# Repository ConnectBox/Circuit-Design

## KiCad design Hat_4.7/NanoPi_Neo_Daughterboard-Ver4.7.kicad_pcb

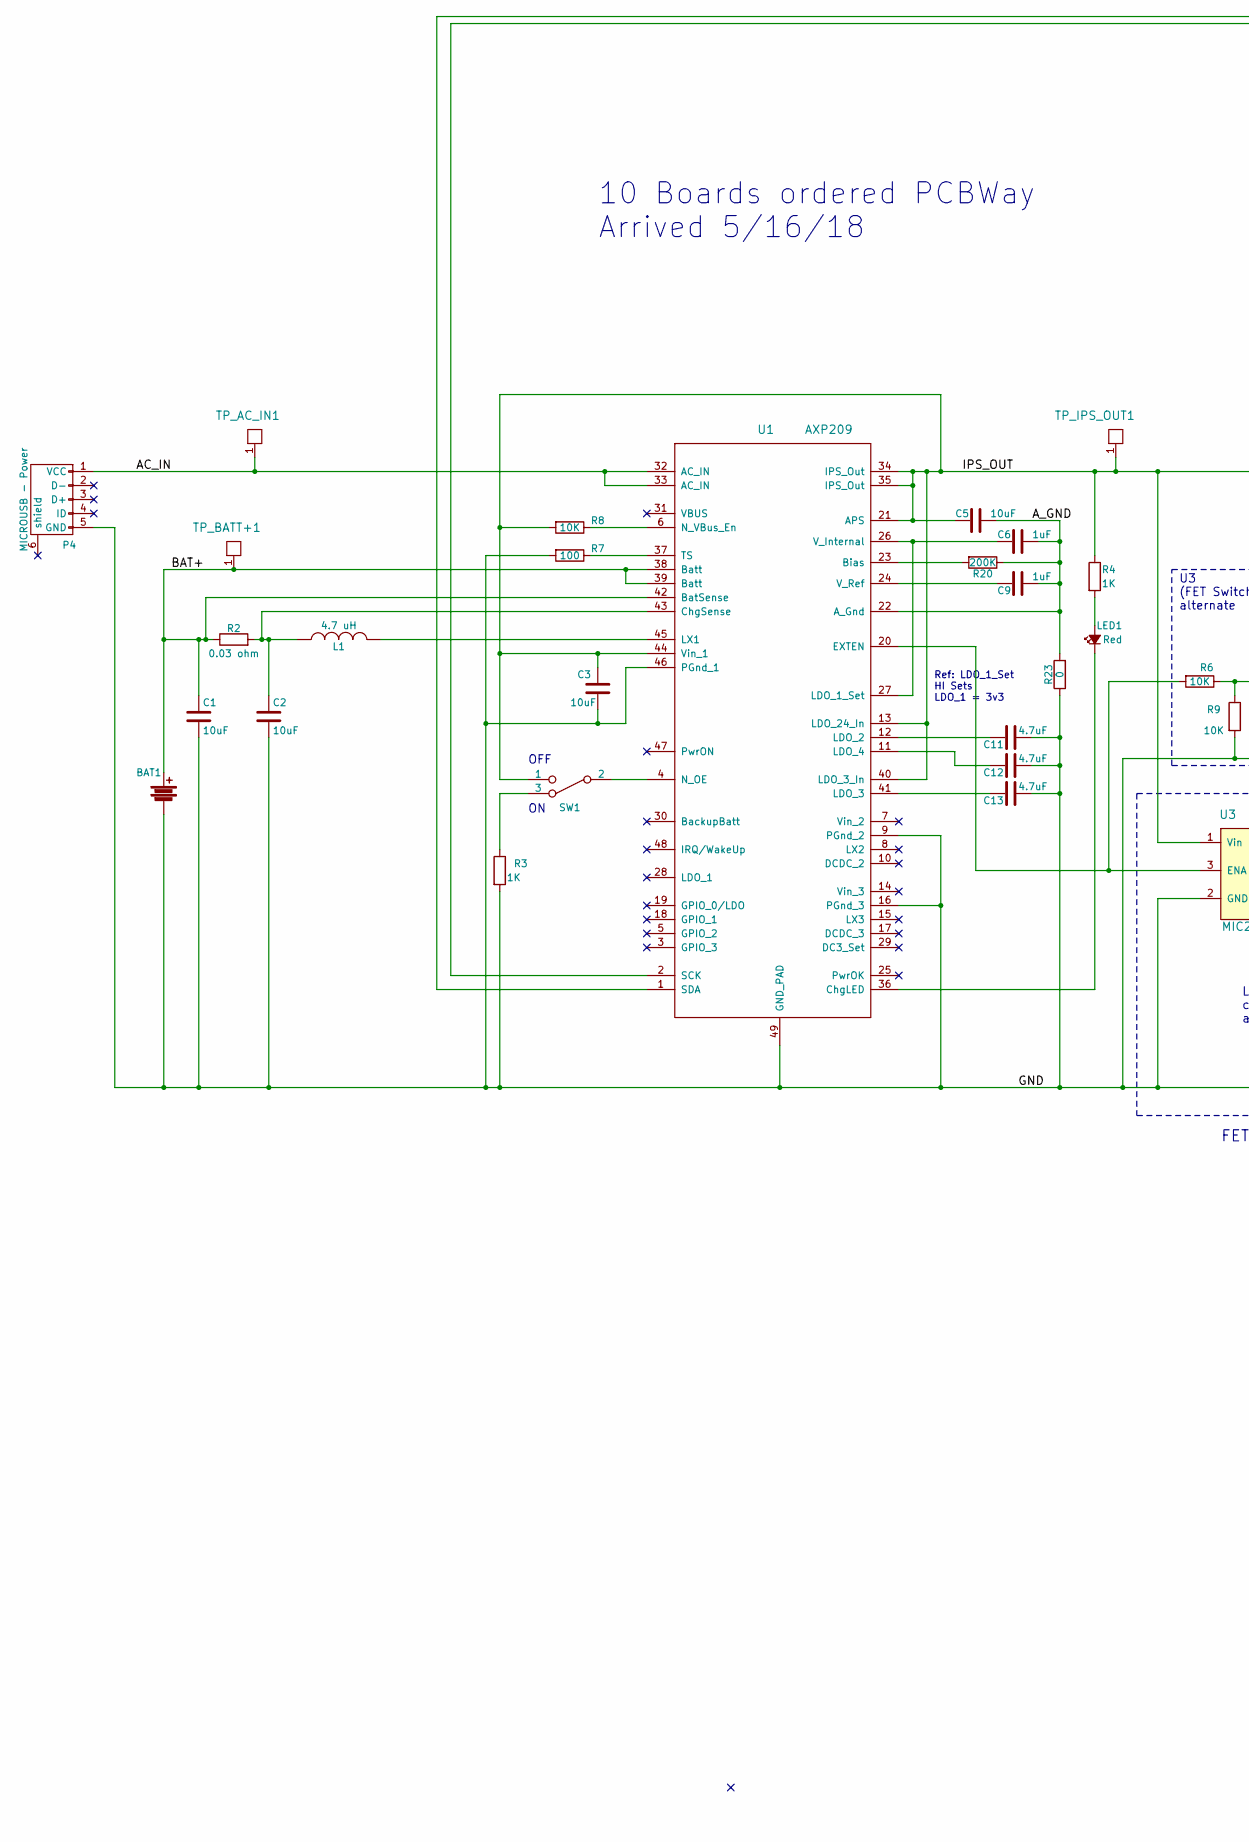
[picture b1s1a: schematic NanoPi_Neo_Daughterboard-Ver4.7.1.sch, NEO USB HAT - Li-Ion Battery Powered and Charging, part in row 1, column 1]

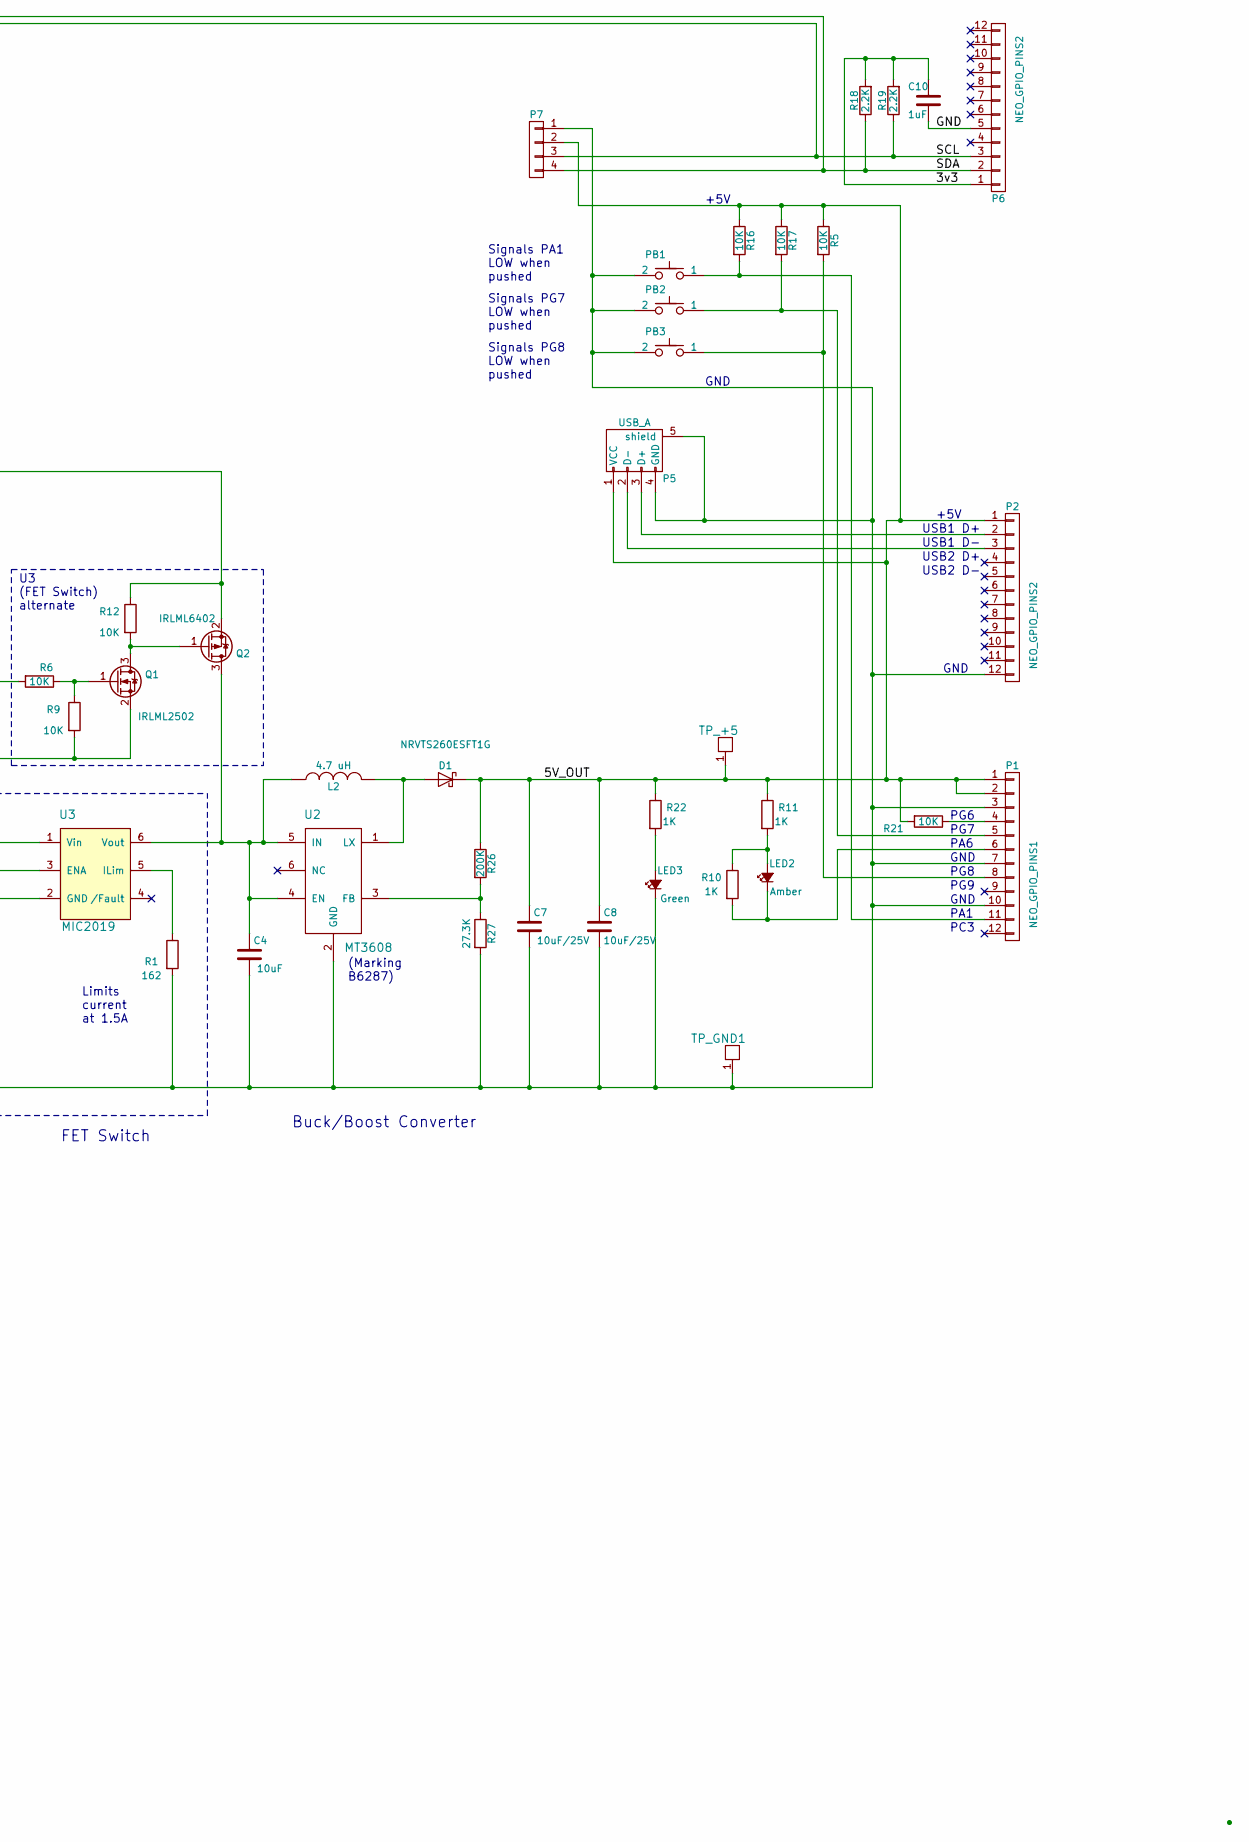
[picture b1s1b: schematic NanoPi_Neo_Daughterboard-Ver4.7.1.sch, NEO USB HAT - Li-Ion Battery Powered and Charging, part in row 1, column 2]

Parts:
BAT1: Battery; Molex_53261
C1, C2, C3, C4, C5: 10uF; C_0805
C6, C9, C10: 1uF; C_0805
C7, C8: 10uF/25V; C_0805
C11, C12, C13: 4.7uF; C_0805
D1: NRVTS260ESFT1G; SMA_Standard
L1, L2: 4.7 uH; INDUCTOR_SMD_6x6-1
LED1: Red; LED_0603
LED2: Amber; LED_0603
LED3: Green; LED_0603
P1: NEO_GPIO_PINS1; PinStrip_12-N
P2: NEO_GPIO_PINS2; PinStrip_12
P4: MICROUSB - Power; USB_Micro-B_Molex_47346-0001
P5: USB_A
P6: NEO_GPIO_PINS2; PinStrip_12-N
P7: CONN_01X04; OLED
PB1, PB2, PB3: SPST-PUSH; SW-TL3305
Q1: IRLML2502; SOT-23
Q2: IRLML6402; SOT-23
R1: 162; R_0805
R2: 0.03 ohm; R_0805
R3, R4, R10, R11, R22: 1K; R_0805
R5, R6, R8, R9, R12, R16, R17, R21: 10K; R_0805
R7: 100; R_0805
R18, R19: 2.2K; R_0805
R20, R26: 200K; R_0805
R23: 0; R_0805
R27: 27.3K; R_0805
SW1: SPDT-2C; SPDT-OS10211
TP_+5: TestPoint; ProbePad
TP_AC_IN1: TestPoint; ProbePad
TP_BATT+1: TestPoint; ProbePad
TP_GND1: TestPoint; ProbePad
TP_IPS_OUT1: TestPoint; ProbePad
U1: AXP209; UQFN-48-1EP_6x6mm_Pitch0.4mm
U2: MT3608; SOT-23-6a
U3: MIC2019; SOT-23-6a

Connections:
/3v3: C10.1, P6.1, R18.2, R19.2
/5V_OUT: C7.1, C8.1, D1.1 (K), P1.1, P1.2, P2.1, P5.1 (VCC), P7.2, R5.1, R11.1, R16.1, R17.1, R21.2, R22.1, R26.1, TP_+5.1; also elsewhere on the board
/AC_IN: P4.1 (VCC), TP_AC_IN1.1, U1.32 (AC_IN), U1.33 (AC_IN)
/A_GND: C5.1, C6.1, C9.1, R20.1, R23.2, U1.22 (A_Gnd)
/BAT+: BAT1.1, C1.1, R2.1, TP_BATT+1.1, U1.38 (Batt), U1.39 (Batt), U1.42 (BatSense)
/GND: BAT1.2, C1.2, C2.2, C3.2, C4.2, C7.2, C8.2, C10.2, C11.1, C12.1, C13.1, LED3.1 (K), P1.3, P1.7, P1.10, P2.12, P4.5 (GND), P5.4 (GND), P5.5 (shield), P6.5, P7.1, PB1.2, PB2.2, PB3.2, Q1.2 (S), R1.2, R3.2, R7.2, R9.2, R23.1, R27.2, TP_GND1.1, U1.9 (PGnd_2), U1.16 (PGnd_3), U1.46 (PGnd_1), U1.49 (GND_PAD), U2.2 (GND), U3.2 (GND); also elsewhere on the board
/IPS_OUT: C3.1, C5.2, Q2.2 (S), R4.1, R8.2, R12.1, SW1.1, TP_IPS_OUT1.1, U1.13 (LDO_24_In), U1.21 (APS), U1.34 (IPS_Out), U1.35 (IPS_Out), U1.40 (LDO_3_In), U1.44 (Vin_1), U3.1 (Vin)
/SCL: P6.3, P7.3, R19.1, U1.2 (SCK)
/SDA: P6.2, P7.4, R18.1, U1.1 (SDA)
unnamed: C2.1, L1.1, R2.2, U1.43 (ChgSense)
unnamed: C4.1, L2.1, Q2.3 (D), U2.4 (EN), U2.5 (IN), U3.6 (Vout)
unnamed: C6.2, U1.26 (V_Internal), U1.27 (LDO_1_Set)
unnamed: C9.2, U1.24 (V_Ref)
unnamed: C11.2, U1.12 (LDO_2)
unnamed: C12.2, U1.11 (LDO_4)
unnamed: C13.2, U1.41 (LDO_3)
unnamed: D1.2 (A), L2.2, U2.1 (LX)
unnamed: L1.2, U1.45 (LX1)
unnamed: LED1.1 (K), U1.36 (ChgLED)
unnamed: LED1.2 (A), R4.2
unnamed: LED2.1 (K), P1.6, R10.2
unnamed: LED2.2 (A), R10.1, R11.2
unnamed: LED3.2 (A), R22.2
unnamed: P1.4, R21.1
unnamed: P1.5, PB2.1, R17.2
unnamed: P1.8, PB3.1, R5.2
unnamed: P1.11, PB1.1, R16.2
unnamed: P2.2, P5.3 (D+)
unnamed: P2.3, P5.2 (D-)
unnamed: Q1.1 (G), R6.1, R9.1
unnamed: Q1.3 (D), Q2.1 (G), R12.2
unnamed: R1.1, U3.5 (ILim)
unnamed: R3.1, SW1.3
unnamed: R6.2, U1.20 (EXTEN), U3.3 (ENA)
unnamed: R7.1, U1.37 (TS)
unnamed: R8.1, U1.6 (N_VBus_En)
unnamed: R20.2, U1.23 (Bias)
unnamed: R26.2, R27.1, U2.3 (FB)
unnamed: SW1.2, U1.4 (N_OE)

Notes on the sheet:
GND
+5V
USB1 D+
USB1 D-
USB2 D+
USB2 D-
PA6
Buck/Boost Converter
PG6
PG7
PG8
PG9
GND
PA1
PC3
Signals PA1 LOW when pushed
Signals PG7 LOW when pushed
OFF
Ref: LDO_1_Set HI Sets LDO_1 = 3v3
Limits current at 1.5A
(Marking B6287)
Signals PG8 LOW when pushed
U3 (FET Switch) alternate
FET Switch
10 Boards ordered PCBWay Arrived 5/16/18

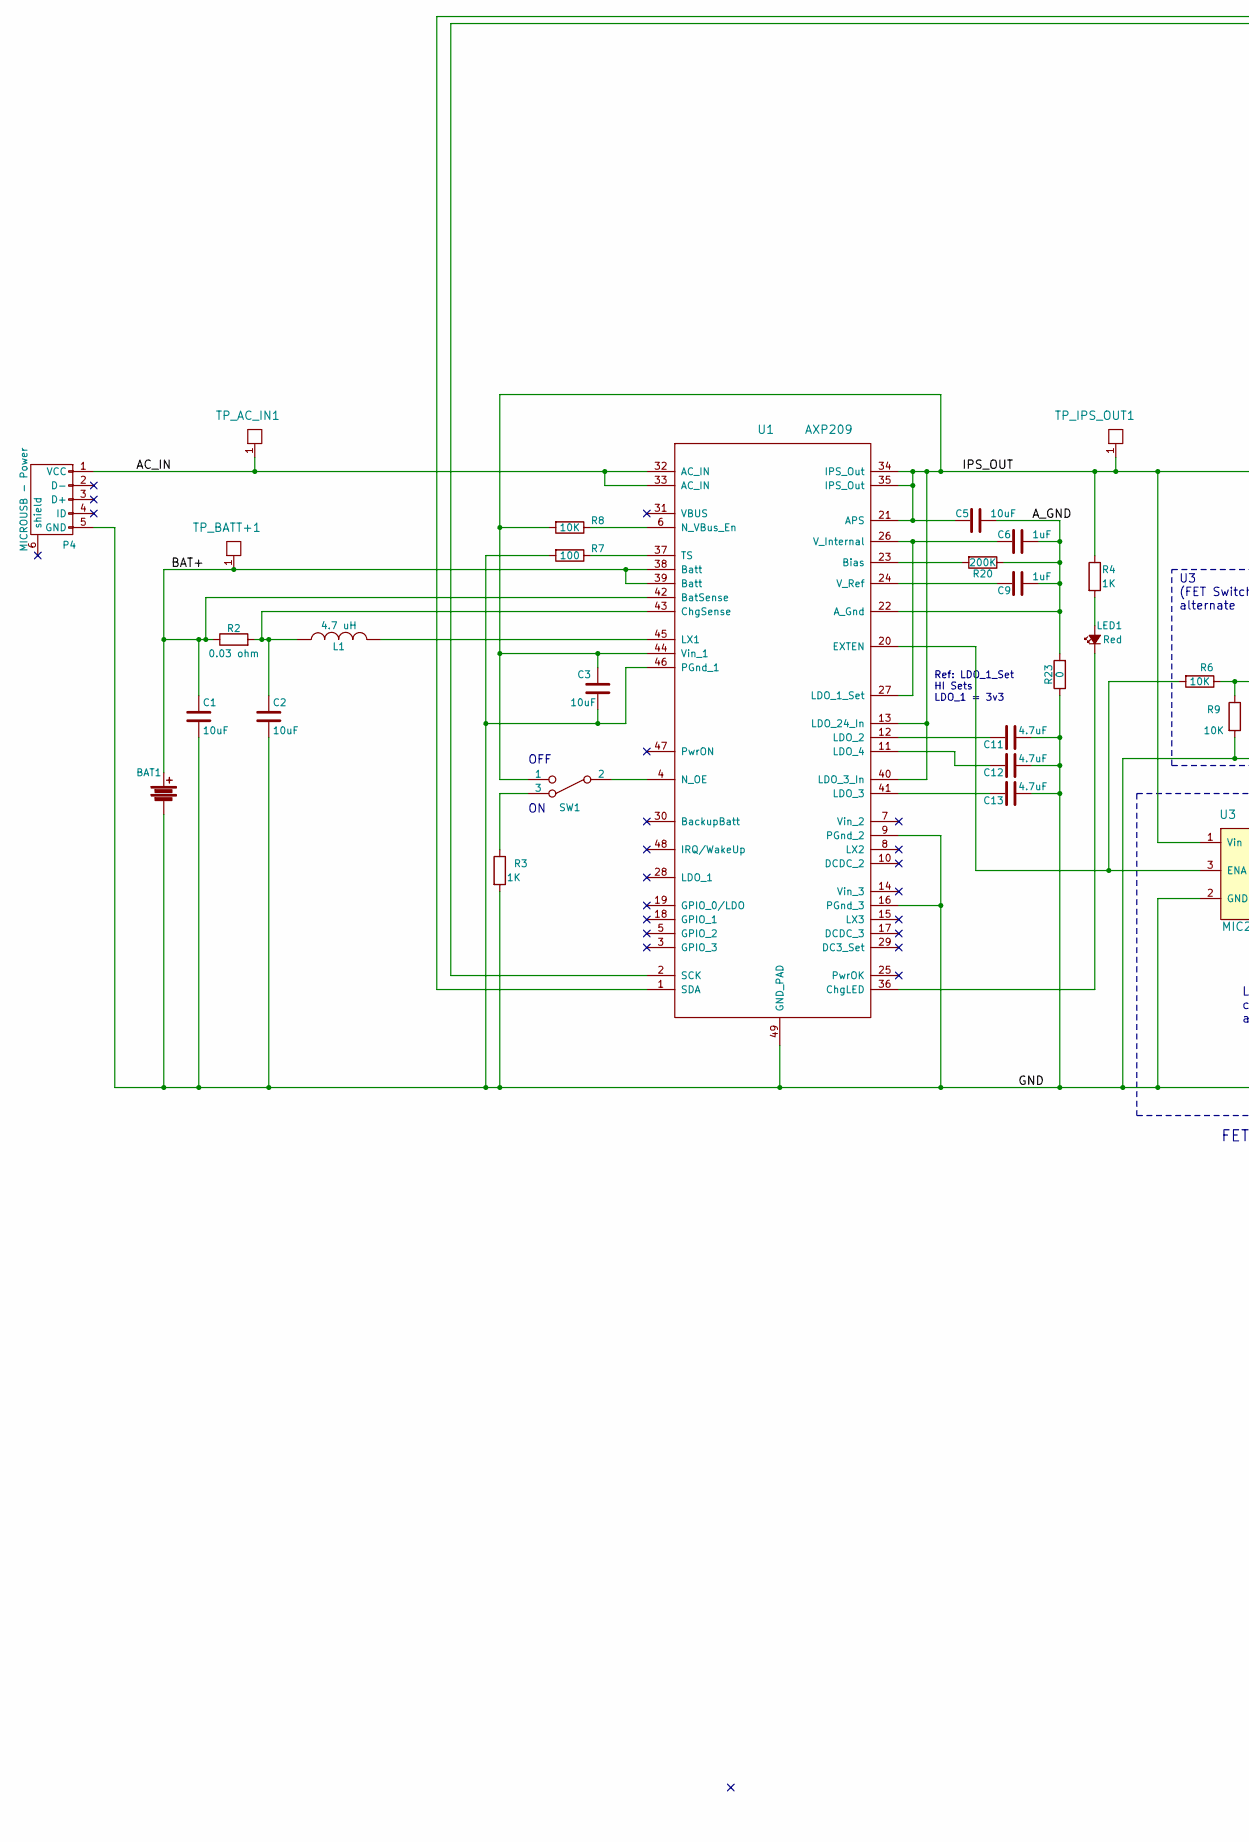
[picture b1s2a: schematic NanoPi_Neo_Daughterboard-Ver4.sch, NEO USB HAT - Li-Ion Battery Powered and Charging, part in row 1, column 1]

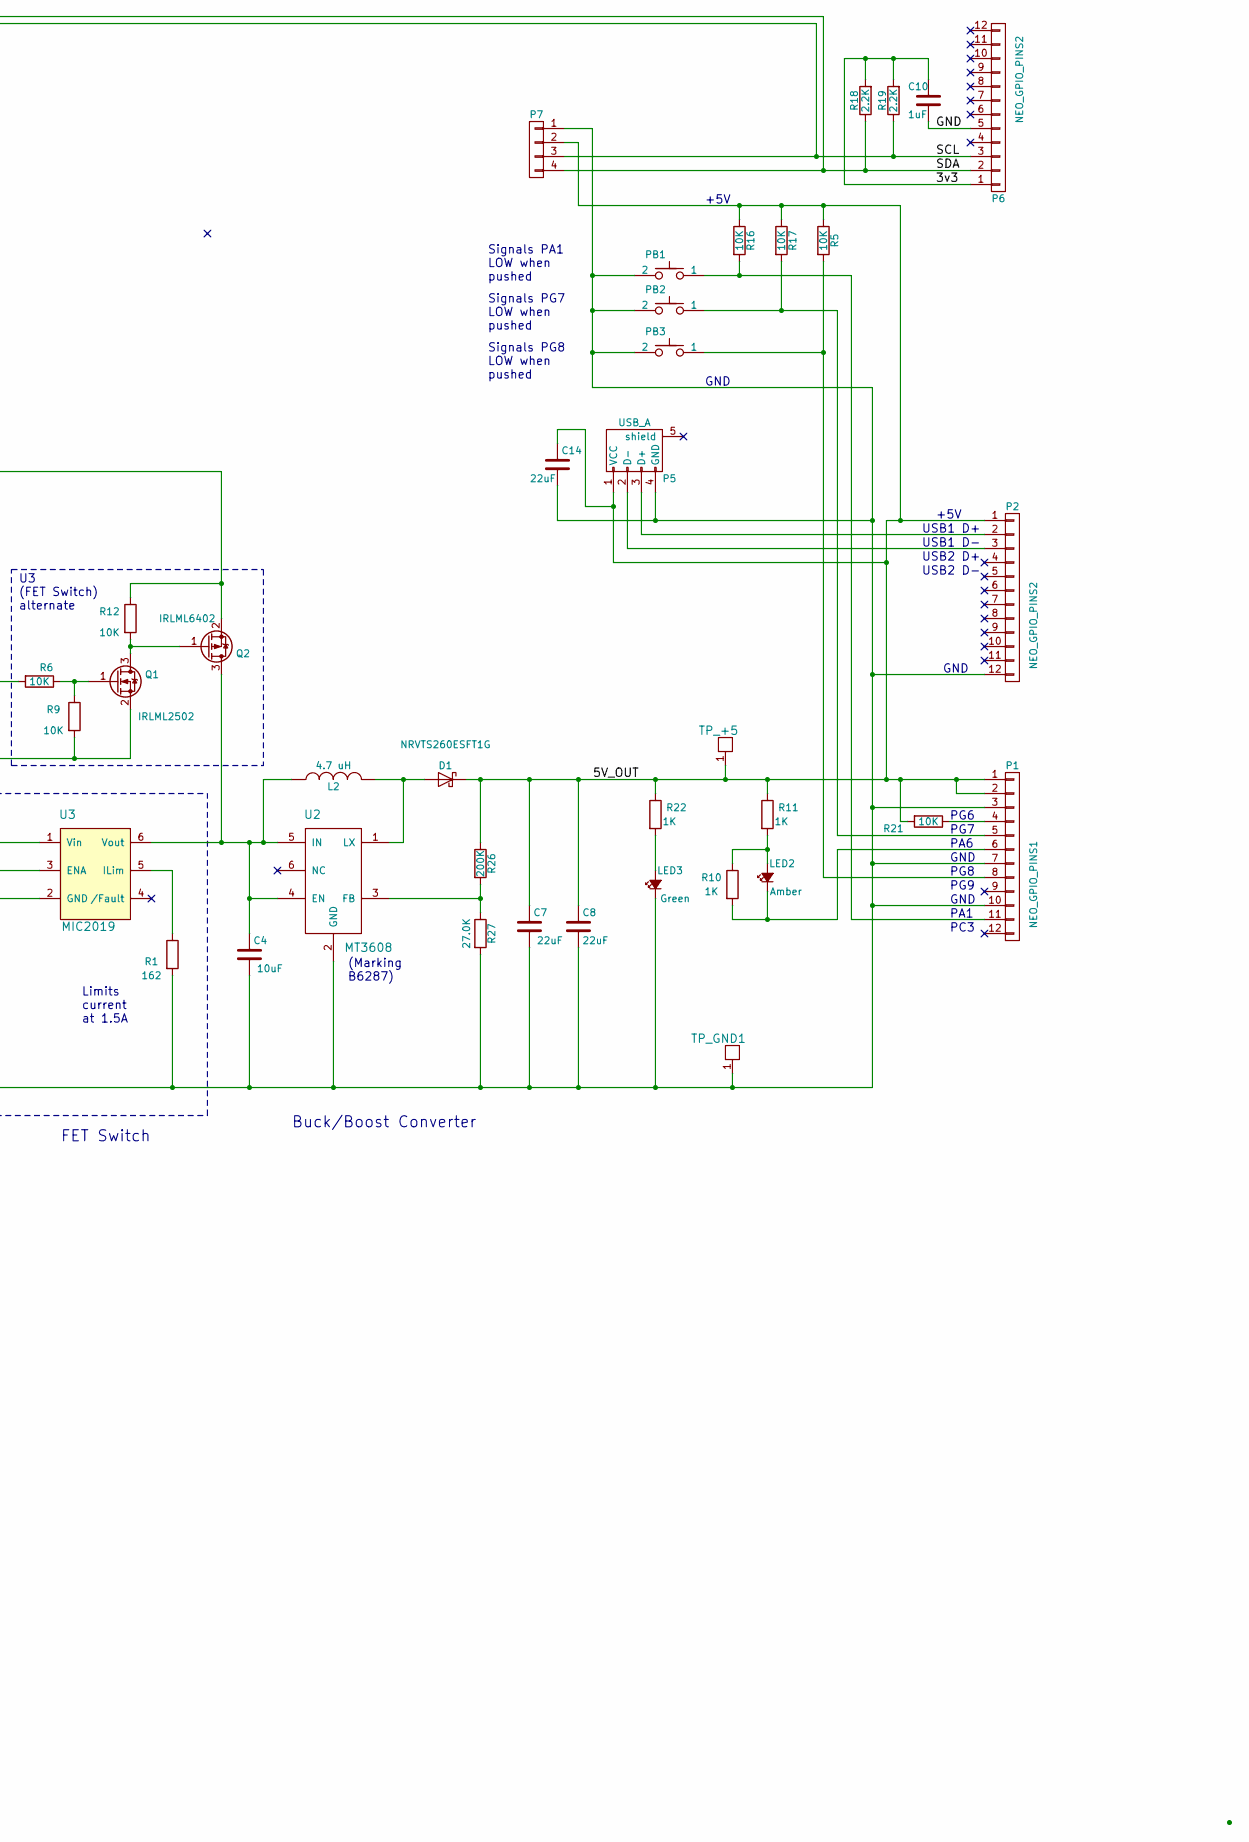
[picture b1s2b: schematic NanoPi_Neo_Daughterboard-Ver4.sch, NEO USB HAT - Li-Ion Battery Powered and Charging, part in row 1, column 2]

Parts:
BAT1: Battery; Molex_53261; Manufacturer P/N 0532610271; DigiKey P/N WM7620CT-ND
C1, C2, C3, C4, C5: 10uF; C_0805; Manufacturer P/N CL21A106MPFNNNE; DigiKey P/N 1276-1144-1-ND
C6, C9, C10: 1uF; C_0805; Manufacturer P/N C0805C105K8PACTU; DigiKey P/N 399-8006-1-ND
C7, C8, C14: 22uF; C_0805; Manufacturer P/N C0805C226M8PAC7800; DigiKey P/N 399-12069-1-ND
C11, C12, C13: 4.7uF; C_0805; Manufacturer P/N CL21B475KPFNNNE; DigiKey P/N 1276-2972-1-ND
D1: NRVTS260ESFT1G; SOD-123FL; Manufacturer P/N NRVTS260ESFT1G; DigiKey P/N NRVTS260ESFT1GOSCT-ND
L1, L2: 4.7 uH; INDUCTOR_SMD_6x6-1; Manufacturer P/N NR6028T4R7M; DigiKey P/N 587-2100-1-ND
LED1: Red; LED_0603; Manufacturer P/N LTST-C191KRKT; DigiKey P/N 160-1447-1-ND
LED2: Amber; LED_0603; Manufacturer P/N LTST-C191KGKT; DigiKey P/N 160-1445-1-ND
LED3: Green; LED_0603; Manufacturer P/N LTST-C191KFKT; DigiKey P/N 160-1446-1-ND
P1: NEO_GPIO_PINS1; PinStrip_12-N; Manufacturer P/N PPPC121LFBN-RC; DigiKey P/N S7045-ND
P2: NEO_GPIO_PINS2; PinStrip_12; Manufacturer P/N PPPC121LFBN-RC; DigiKey P/N S7045-ND
P4: MICROUSB - Power; USB_Micro-B_Molex_47346-0001; Manufacturer P/N 10118192-0001LF; DigiKey P/N 609-4613-1-ND
P5: USB_A; Manufacturer P/N 87520-0010BLF; DigiKey P/N 609-1045-ND
P6: NEO_GPIO_PINS2; PinStrip_12-N; Manufacturer P/N PPPC051LFBN-RC; DigiKey P/N S7038-ND
P7: CONN_01X04; OLED; Manufacturer P/N PPPC041LFBN-RC; DigiKey P/N S7037-ND
PB1, PB2, PB3: SPST-PUSH; SW-TL3305; Manufacturer P/N TL3305AF260QG; DigiKey P/N EG5353CT-ND
Q1: IRLML2502; SOT-23
Q2: IRLML6402; SOT-23
R1: 162; R_0805; Manufacturer P/N RC0805FR-07162R; DigiKey P/N 311-162CRCT-ND
R2: 0.03 ohm; R_0805; Manufacturer P/N ERJ-6CWFR030V; DigiKey P/N P19207CT-ND
R3, R4, R10, R11, R22: 1K; R_0805; Manufacturer P/N RC0805FR-071KL; DigiKey P/N 311-1.00KCRCT-ND
R5, R8, R16, R17, R21: 10K; R_0805; Manufacturer P/N RC0805FR-0710KL; DigiKey P/N 311-10.0KCRCT-ND
R6, R9, R12: 10K; R_0805
R7: 100; R_0805; Manufacturer P/N RC0805FR-07100RL; DigiKey P/N 311-100CRCT-ND
R18, R19: 2.2K; R_0805; Manufacturer P/N RC0805FR-072K2L; DigiKey P/N 311-2.20KCRCT-ND
R20, R26: 200K; R_0805; Manufacturer P/N RC0805FR-07200KL; DigiKey P/N 311-200KCRCT-ND
R23: 0; R_0805; Manufacturer P/N RC0805FR-070RL; DigiKey P/N 311-0.0CRCT-ND
R27: 27.0K; R_0805; Manufacturer P/N RC0805FR-0727KL; DigiKey P/N 311-27.0KCRCT-ND
SW1: SPDT-2C; SPDT-OS10211; Manufacturer P/N OS102011MA1QN1; DigiKey P/N CKN9559-ND or CKN9560-ND
TP_+5: TestPoint; ProbePad
TP_AC_IN1: TestPoint; ProbePad
TP_BATT+1: TestPoint; ProbePad
TP_GND1: TestPoint; ProbePad
TP_IPS_OUT1: TestPoint; ProbePad
U1: AXP209; UQFN-48-1EP_6x6mm_Pitch0.4mm_75; Manufacturer P/N AXP209
U2: MT3608; SOT-23-6a; Manufacturer P/N MT3608
U3: MIC2019; SOT-23-6a; Manufacturer P/N MIC2019YM6-TR; DigiKey P/N 576-2595-1-ND

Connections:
/3v3: C10.1, P6.1, R18.2, R19.2
/5V_OUT: C7.1, C8.1, C14.1, D1.1 (K), P1.1, P1.2, P2.1, P5.1 (VCC), P7.2, R5.1, R11.1, R16.1, R17.1, R21.2, R22.1, R26.1, TP_+5.1
/AC_IN: P4.1 (VCC), TP_AC_IN1.1, U1.32 (AC_IN), U1.33 (AC_IN)
/A_GND: C5.1, C6.1, C9.1, R20.1, R23.2, U1.22 (A_Gnd)
/BAT+: BAT1.1, C1.1, R2.1, TP_BATT+1.1, U1.38 (Batt), U1.39 (Batt), U1.42 (BatSense)
/GND: BAT1.2, C1.2, C2.2, C3.2, C4.2, C7.2, C8.2, C10.2, C11.1, C12.1, C13.1, C14.2, LED3.1 (K), P1.3, P1.7, P1.10, P2.12, P4.5 (GND), P5.4 (GND), P5.5 (shield), P6.5, P7.1, PB1.2, PB2.2, PB3.2, Q1.2 (S), R1.2, R3.2, R7.2, R9.2, R23.1, R27.2, TP_GND1.1, U1.9 (PGnd_2), U1.16 (PGnd_3), U1.46 (PGnd_1), U1.49 (GND_PAD), U2.2 (GND), U3.2 (GND)
/IPS_OUT: C3.1, C5.2, Q2.2 (S), R4.1, R8.2, R12.1, SW1.1, TP_IPS_OUT1.1, U1.13 (LDO_24_In), U1.21 (APS), U1.34 (IPS_Out), U1.35 (IPS_Out), U1.40 (LDO_3_In), U1.44 (Vin_1), U3.1 (Vin)
/SCL: P6.3, P7.3, R19.1, U1.2 (SCK)
/SDA: P6.2, P7.4, R18.1, U1.1 (SDA)
unnamed: C2.1, L1.1, R2.2, U1.43 (ChgSense)
unnamed: C4.1, L2.1, Q2.3 (D), U2.4 (EN), U2.5 (IN), U3.6 (Vout)
unnamed: C6.2, U1.26 (V_Internal), U1.27 (LDO_1_Set)
unnamed: C9.2, U1.24 (V_Ref)
unnamed: C11.2, U1.12 (LDO_2)
unnamed: C12.2, U1.11 (LDO_4)
unnamed: C13.2, U1.41 (LDO_3)
unnamed: D1.2 (A), L2.2, U2.1 (LX)
unnamed: L1.2, U1.45 (LX1)
unnamed: LED1.1 (K), U1.36 (ChgLED)
unnamed: LED1.2 (A), R4.2
unnamed: LED2.1 (K), P1.6, R10.2
unnamed: LED2.2 (A), R10.1, R11.2
unnamed: LED3.2 (A), R22.2
unnamed: P1.4, R21.1
unnamed: P1.5, PB2.1, R17.2
unnamed: P1.8, PB3.1, R5.2
unnamed: P1.11, PB1.1, R16.2
unnamed: P2.2, P5.3 (D+)
unnamed: P2.3, P5.2 (D-)
unnamed: Q1.1 (G), R6.1, R9.1
unnamed: Q1.3 (D), Q2.1 (G), R12.2
unnamed: R1.1, U3.5 (ILim)
unnamed: R3.1, SW1.3
unnamed: R6.2, U1.20 (EXTEN), U3.3 (ENA)
unnamed: R7.1, U1.37 (TS)
unnamed: R8.1, U1.6 (N_VBus_En)
unnamed: R20.2, U1.23 (Bias)
unnamed: R26.2, R27.1, U2.3 (FB)
unnamed: SW1.2, U1.4 (N_OE)

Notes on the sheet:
GND
+5V
USB1 D+
USB1 D-
USB2 D+
USB2 D-
PA6
Buck/Boost Converter
PG6
PG7
PG8
PG9
GND
PA1
PC3
Signals PA1 LOW when pushed
Signals PG7 LOW when pushed
OFF
Ref: LDO_1_Set HI Sets LDO_1 = 3v3
Limits current at 1.5A
(Marking B6287)
Signals PG8 LOW when pushed
U3 (FET Switch) alternate
FET Switch

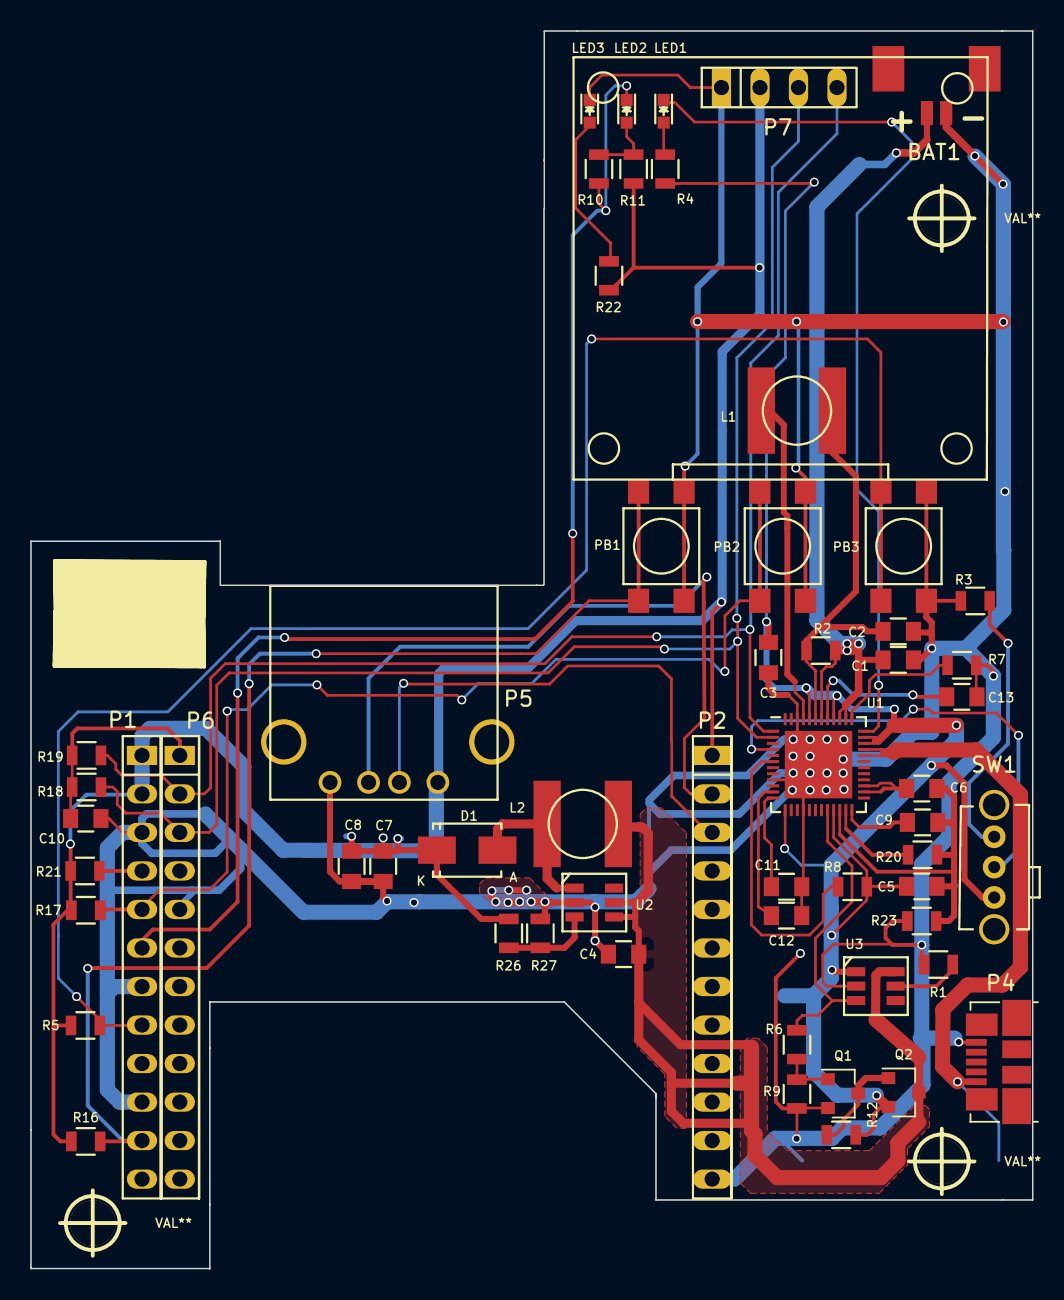
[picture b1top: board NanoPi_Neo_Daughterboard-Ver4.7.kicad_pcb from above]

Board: 2 copper layers, 66.0 x 81.6 mm, 65 parts (0 on the bottom side), 39 nets.

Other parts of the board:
hole_3mm, hole_3mm#2, hole_3mm#3: VAL**; hole_3mm

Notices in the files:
Hat_4.7/NanoPi_Neo_Daughterboard-Ver4.7.kicad_pcb:
Copyright 2018, ConnectBox Project
